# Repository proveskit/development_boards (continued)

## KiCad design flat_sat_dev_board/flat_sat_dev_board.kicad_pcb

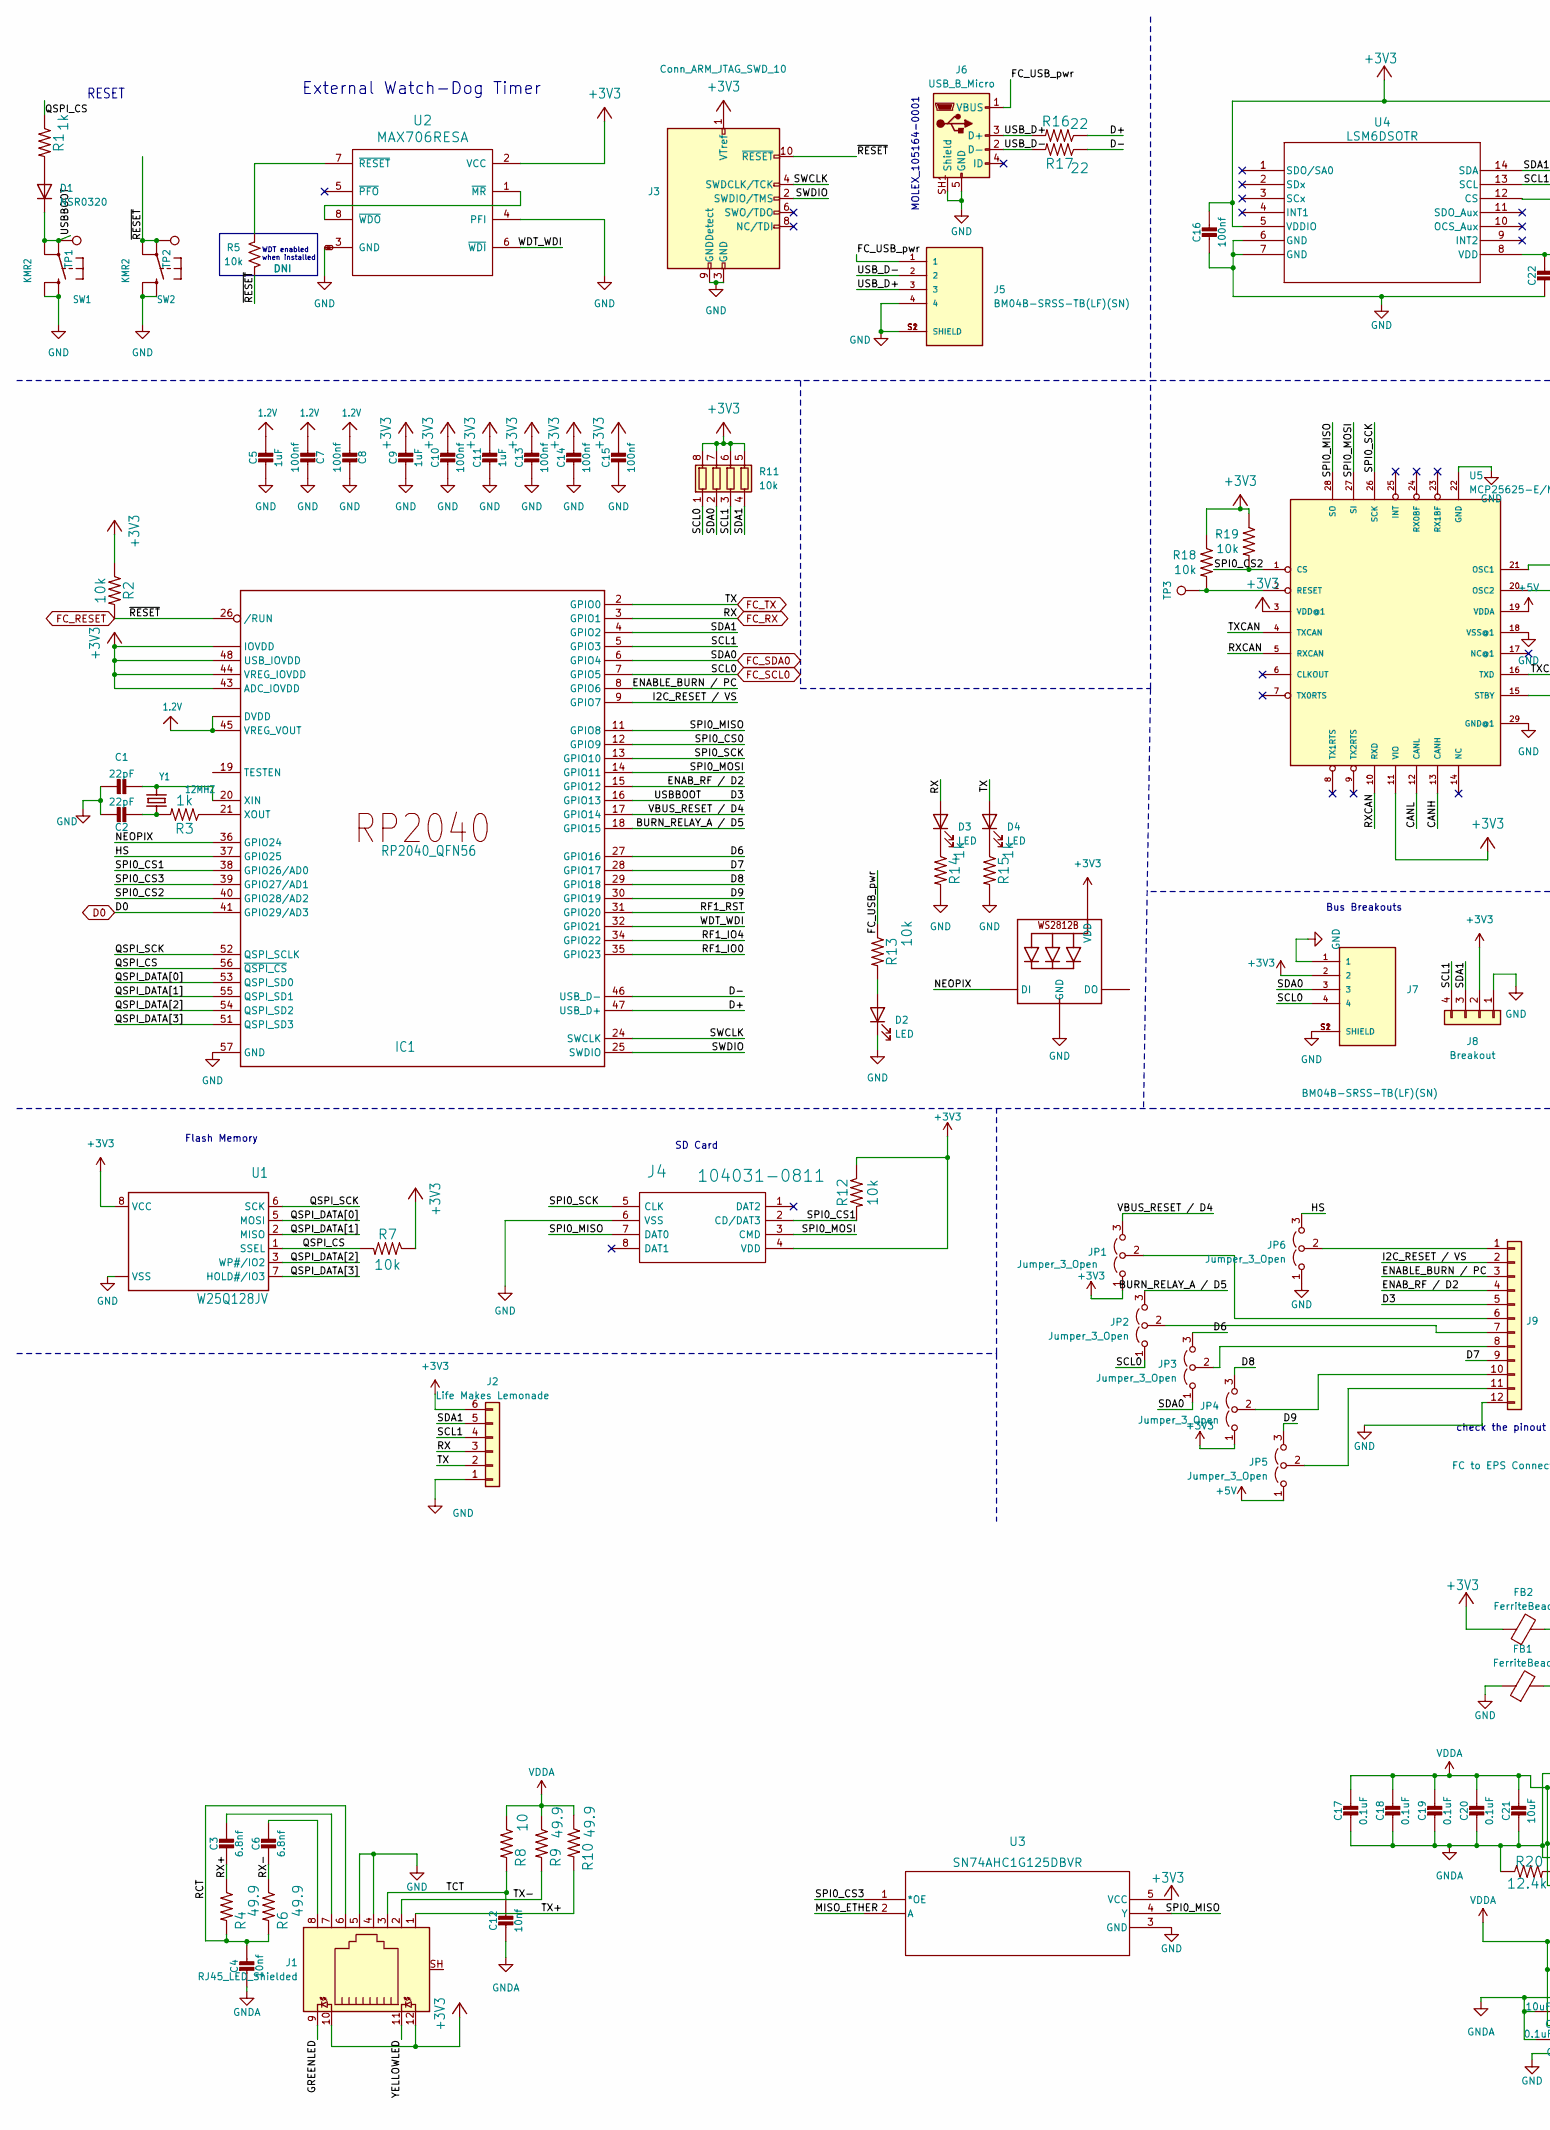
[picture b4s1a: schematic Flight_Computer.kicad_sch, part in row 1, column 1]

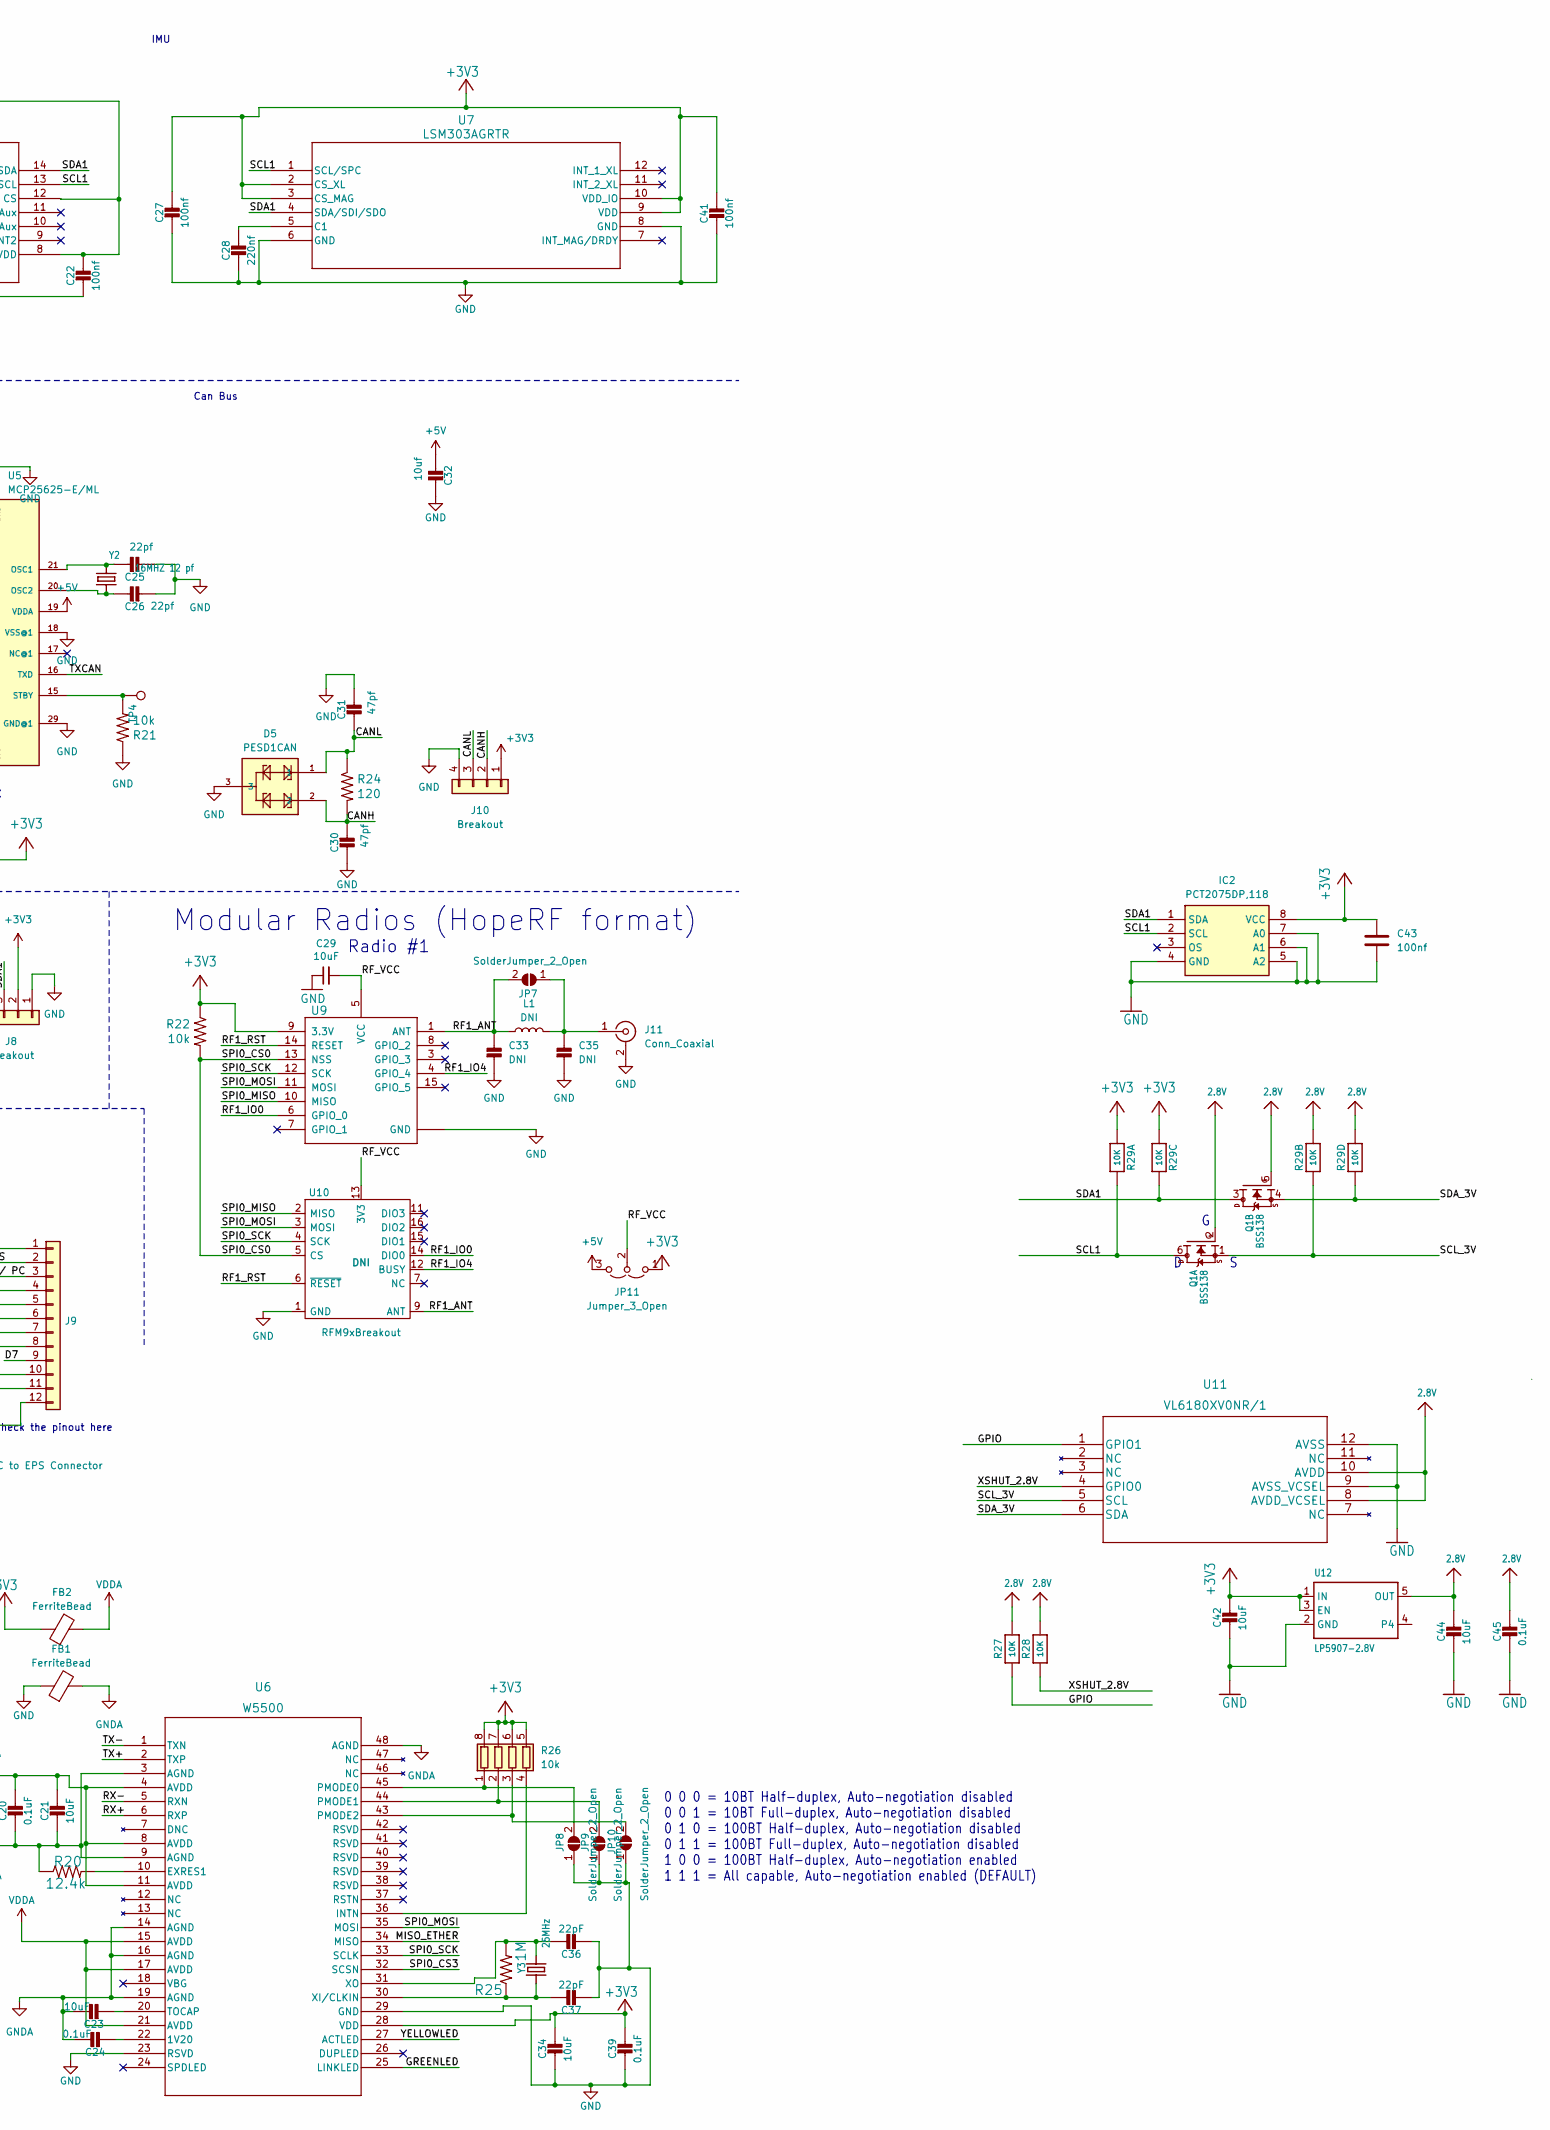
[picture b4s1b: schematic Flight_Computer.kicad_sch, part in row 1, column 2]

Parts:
C1, C2, C36, C37: 22pF; C_0402_1005Metric
C3, C6: 6.8nf; C_0402_1005Metric
C4, C12: 10nf; C_0402_1005Metric
C5, C9, C11: 1uF; C_0603_1608Metric
C7, C8, C10, C13, C14, C15, C16, C22, C27, C41: 100nf; C_0402_1005Metric
C17, C18, C19, C20, C24, C39, C45: 0.1uF; C_0603_1608Metric
C21, C23, C34, C42, C44: 10uF; C_0805_2012Metric
C25, C26: 22pf; C_0402_1005Metric
C28: 220nf; C_0402_1005Metric
C29: 10uF; C_0603_1608Metric
C30, C31: 47pf; C_0402_1005Metric
C32: 10uf; C_0603_1608Metric
C33, C35: DNI; C_0603_1608Metric
C43: 100nf; C_0603_1608Metric
D1: NSR0320; D_SOD-323F
D2, D3, D4: LED; LED_0603_1608Metric
D5: PESD1CAN; SOT-23-3
FB1, FB2: FerriteBead; R_0603_1608Metric
IC1: RP2040_QFN56; QFN-56-1EP_7x7mm_P0.4mm_EP3.2x3.2mm_ThermalVias
IC2: PCT2075DP,118; TSSOP-8_3x3mm_P0.65mm; Mouser Part Number 771-PCT2075DP118
J1: RJ45_LED_Shielded; RB1-125BAG1A_WIZ
J2: Life Makes Lemonade; PinHeader_1x06_P2.54mm_Vertical
J3: Conn_ARM_JTAG_SWD_10; JTAG_2X05_1.27MM_BOX_NOCREAM
J4: 104031-0811; microSD_HC_Molex_104031-0811; Manufacturer_Part_Number 104031-0811; Mouser Part Number 538-104031-0811
J5, J7: BM04B-SRSS-TB(LF)(SN); JST_BM04B-SRSS-TB(LF)(SN); PARTREV N/A
J6: USB_B_Micro; MOLEX_105164-0001
J8: Breakout; JST_SH_SM04B-SRSS-TB_1x04-1MP_P1.00mm_Horizontal
J9: FC to EPS Connector; Molex_Pico-Lock_504050-1291_1x12-1MP_P1.50mm_Horizontal
J10: Breakout; JST_SH_BM04B-SRSS-TB_1x04-1MP_P1.00mm_Vertical
J11: Conn_Coaxial; SMA_Amphenol_901-144_Vertical
JP1, JP2, JP3, JP4, JP5, JP6, JP11: Jumper_3_Open; SolderJumper-3_P1.3mm_Open_RoundedPad1.0x1.5mm_NumberLabels
JP7, JP8, JP9, JP10: SolderJumper_2_Open; SolderJumper-2_P1.3mm_Open_RoundedPad1.0x1.5mm
L1: DNI; R_0603_1608Metric
LED1: WS2812B_SK6812_1515; LED_WS2812B_PLCC4_5.0x5.0mm_P3.2mm
Q1: BSS138; SOT-363_SC-70-6
R1, R14, R15: 1k; R_0603_1608Metric
R2, R5, R7, R12, R13, R18, R19, R21, R22: 10k; R_0603_1608Metric
R3: 1k; R_0402_1005Metric
R4, R6, R9, R10: 49.9; R_0603_1608Metric
R8: 10; R_0603_1608Metric
R11, R26: 10k; R_Array_Convex_4x0603
R16, R17: 22; R_0603_1608Metric
R20: 12.4k; R_0603_1608Metric
R24: 120; R_0603_1608Metric
R25: 1M; R_0603_1608Metric
R27, R28: 10K; R_0603_1608Metric
R29: 10K; R_Array_Convex_4x0603
SW1, SW2: KMR2; BTN_KMR2_4.6X2.8
TP1: USBBOOT; TestPoint_Loop_D1.80mm_Drill1.0mm_Beaded
TP2, TP3: RESET; TestPoint_Loop_D1.80mm_Drill1.0mm_Beaded
TP4: Standby; TestPoint_Loop_D1.80mm_Drill1.0mm_Beaded
U1: W25Q128JV; SOIC-8_5.275x5.275mm_P1.27mm
U2: MAX706RESA; SO-8_3.9x4.9mm_P1.27mm; Manufacturer_Part_Number MAX706RESA
U3: SN74AHC1G125DBVR; SOT-23-5
U4: LSM6DSOTR; LGA-14_3x2.5mm_P0.5mm_LayoutBorder3x4y
U5: MCP25625-E/ML; QFN-28-1EP_6x6mm_P0.65mm_EP4.25x4.25mm
U6: W5500; LQFP-48_7x7mm_P0.5mm
U7: LSM303AGRTR; LGA-12_2x2mm_P0.5mm
U9: RFM98PW; Manufacturer_Part_Number RFM98PW
U10: RFM9xBreakout; HOPERF_RFM9XW_SMD
U11: VL6180XV0NR/1; VL6180
U12: LP5907-2.8V; SOT-23-5
Y1: 12MHZ; Crystal_SMD_2520-4Pin_2.5x2.0mm
Y2: 16MHZ 12 pf; Crystal_SMD_2520-4Pin_2.5x2.0mm
Y3: 25MHz; Crystal_SMD_3225-4Pin_3.2x2.5mm

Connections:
1.2V: C5.1, C7.2, C8.2, IC1.23 (DVDD), IC1.45 (VREG_VOUT), IC1.50 (DVDD); also elsewhere on the board
2.8V: C44.1, C45.1, Q1.2 (G), Q1.5 (G), R27.2, R28.2, R29.2 (1), R29.4 (1), U11.8 (AVDD_VCSEL), U11.10 (AVDD), U12.5 (OUT)
+3V3: C9.1, C10.1, C11.1, C13.1, C14.1, C15.1, C16.1, C22.1, C27.1, C34.1, C39.1, C41.1, C42.1, C43.1, FB2.1, IC1.1 (IOVDD), IC1.10 (IOVDD), IC1.22 (IOVDD), IC1.33 (IOVDD), IC1.42 (IOVDD), IC1.43 (ADC_IOVDD), IC1.44 (VREG_IOVDD), IC1.48 (USB_IOVDD), IC1.49 (IOVDD), IC2.8 (VCC), J1.10, J1.12, J2.6, J3.1 (VTref), J4.4 (VDD), J7.2, J8.2, J10.1, JP1.1 (A), JP4.1 (A), JP11.1 (A), LED1.1 (VDD), R2.1, R7.1, R11.5 (R4.2), R11.6 (R3.2), R11.7 (R2.2), R11.8 (R1.2), R12.1, R18.1, R19.1, R22.1, R26.5 (R4.2), R26.6 (R3.2), R26.7 (R2.2), R26.8 (R1.2), R29.1, R29.3 (1), U1.8 (VCC), U2.2 (VCC), U3.5 (VCC), U4.5 (VDDIO), U4.8 (VDD), U4.12 (CS), U5.3 (VDD@1), U5.11 (VIO), U6.28 (VDD), U7.2 (CS_XL), U7.3 (CS_MAG), U7.9 (VDD), U7.10 (VDD_IO), U9.9 (3.3V), U12.1 (IN), U12.3 (EN); also elsewhere on the board
+5V: C32.2, JP5.1 (A), JP11.3 (B), U5.19 (VDDA); also elsewhere on the board
/Flight Computer Stuff/BURN_RELAY_A / D5: IC1.18 (GPIO15), JP2.3 (B)
/Flight Computer Stuff/CANH: C30.2, D5.2, J10.2, R24.2, U5.13 (CANH)
/Flight Computer Stuff/CANL: C31.1, D5.1, J10.3, R24.1, U5.12 (CANL)
/Flight Computer Stuff/D3: D1.1 (K), IC1.16 (GPIO13), J9.5, SW1.A, SW1.A' (P1), TP1.1
/Flight Computer Stuff/D6: IC1.27 (GPIO16), JP3.3 (B)
/Flight Computer Stuff/D7: IC1.28 (GPIO17), J9.9
/Flight Computer Stuff/D8: IC1.29 (GPIO18), JP4.3 (B)
/Flight Computer Stuff/D9: IC1.30 (GPIO19), JP5.3 (B)
/Flight Computer Stuff/D+: IC1.47 (USB_D+), R16.1
/Flight Computer Stuff/D-: IC1.46 (USB_D-), R17.1
/Flight Computer Stuff/ENABLE_BURN / PC: IC1.8 (GPIO6), J9.3
/Flight Computer Stuff/ENAB_RF / D2: IC1.15 (GPIO12), J9.4
/Flight Computer Stuff/FC_USB_pwr: J5.1, J6.1 (VBUS), R13.1
/Flight Computer Stuff/GPIO: R27.1, U11.1 (GPIO1)
/Flight Computer Stuff/GREENLED: J1.9, U6.25 (LINKLED)
/Flight Computer Stuff/HS: IC1.37 (GPIO25), JP6.3 (B)
/Flight Computer Stuff/I2C_RESET / VS: IC1.9 (GPIO7), J9.2
/Flight Computer Stuff/MISO_ETHER: U3.2 (A), U6.34 (MISO)
/Flight Computer Stuff/NEOPIX: IC1.36 (GPIO24), LED1.4 (DI)
/Flight Computer Stuff/QSPI_CS: IC1.56 (~QSPI_CS), R1.1, R7.2, U1.1 (SSEL)
/Flight Computer Stuff/QSPI_DATA[0]: IC1.53 (QSPI_SD0), U1.5 (MOSI)
/Flight Computer Stuff/QSPI_DATA[1]: IC1.55 (QSPI_SD1), U1.2 (MISO)
/Flight Computer Stuff/QSPI_DATA[2]: IC1.54 (QSPI_SD2), U1.3 (WP#/IO2)
/Flight Computer Stuff/QSPI_DATA[3]: IC1.51 (QSPI_SD3), U1.7 (HOLD#/IO3)
/Flight Computer Stuff/QSPI_SCK: IC1.52 (QSPI_SCLK), U1.6 (SCK)
/Flight Computer Stuff/RCT: C4.1, J1.6, R4.2, R6.2
/Flight Computer Stuff/RF1_ANT: C33.1, JP7.2 (B), L1.1, U9.1 (ANT), U10.9 (ANT)
/Flight Computer Stuff/RF1_IO0: IC1.35 (GPIO23), U9.6 (GPIO_0), U10.14 (DIO0)
/Flight Computer Stuff/RF1_IO4: IC1.34 (GPIO22), U9.4 (GPIO_4), U10.12 (BUSY)
/Flight Computer Stuff/RF1_RST: IC1.31 (GPIO20), U9.14 (RESET), U10.6 (~RESET)
/Flight Computer Stuff/RF_VCC: C29.2, JP11.2 (C), U9.5 (VCC), U10.13 (3V3)
/Flight Computer Stuff/RX+: C3.2, R4.1, U6.6 (RXP)
/Flight Computer Stuff/RX-: C6.2, R6.1, U6.5 (RXN)
/Flight Computer Stuff/RXCAN: U5.5 (RXCAN), U5.10 (RXD)
/Flight Computer Stuff/SCL1: IC1.5 (GPIO3), IC2.2 (SCL), J2.4, J8.4, Q1.6 (D), R11.3 (R3.1), R29.8 (2), U4.13 (SCL), U7.1 (SCL/SPC)
/Flight Computer Stuff/SCL_3V: Q1.1 (S), R29.7 (2), U11.5 (SCL)
/Flight Computer Stuff/SDA1: IC1.4 (GPIO2), IC2.1 (SDA), J2.5, J8.3, Q1.3 (D), R11.4 (R4.1), R29.6 (2), U4.14 (SDA), U7.4 (SDA/SDI/SDO)
/Flight Computer Stuff/SDA_3V: Q1.4 (S), R29.5 (2), U11.6 (SDA)
/Flight Computer Stuff/SPI0_CS0: IC1.12 (GPIO9), R22.2, U9.13 (NSS), U10.5 (CS)
/Flight Computer Stuff/SPI0_CS1: IC1.38 (GPIO26/AD0), J4.2 (CD/DAT3), R12.2
/Flight Computer Stuff/SPI0_CS2: IC1.40 (GPIO28/AD2), R19.2, U5.1 (CS)
/Flight Computer Stuff/SPI0_CS3: IC1.39 (GPIO27/AD1), U3.1 (*OE), U6.32 (SCSN)
/Flight Computer Stuff/SPI0_MISO: IC1.11 (GPIO8), J4.7 (DAT0), U3.4 (Y), U5.28 (SO), U9.10 (MISO), U10.2 (MISO)
/Flight Computer Stuff/SPI0_MOSI: IC1.14 (GPIO11), J4.3 (CMD), U5.27 (SI), U6.35 (MOSI), U9.11 (MOSI), U10.3 (MOSI)
/Flight Computer Stuff/SPI0_SCK: IC1.13 (GPIO10), J4.5 (CLK), U5.26 (SCK), U6.33 (SCLK), U9.12 (SCK), U10.4 (SCK)
/Flight Computer Stuff/SWCLK: IC1.24 (SWCLK), J3.4 (SWDCLK/TCK)
/Flight Computer Stuff/SWDIO: IC1.25 (SWDIO), J3.2 (SWDIO/TMS)
/Flight Computer Stuff/TCT: C12.1, J1.3, R8.2
/Flight Computer Stuff/TX+: J1.1, R10.2, U6.2 (TXP)
/Flight Computer Stuff/TX-: J1.2, R9.2, U6.1 (TXN)
/Flight Computer Stuff/TXCAN: U5.4 (TXCAN), U5.16 (TXD)
/Flight Computer Stuff/USB_D+: J5.3, J6.3 (D+), R16.2
/Flight Computer Stuff/USB_D-: J5.2, J6.2 (D-), R17.2
/Flight Computer Stuff/VBUS_RESET / D4: IC1.17 (GPIO14), JP1.3 (B)
/Flight Computer Stuff/WDT_WDI: IC1.32 (GPIO21), U2.6 (~WDI)
/Flight Computer Stuff/XSHUT_2.8V: R28.1, U11.4 (GPIO0)
/Flight Computer Stuff/YELLOWLED: J1.11, U6.27 (ACTLED)
D0: IC1.41 (GPIO29/AD3); also elsewhere on the board
FC_RESET: IC1.26 (/RUN), J3.10 (~RESET), R2.2, R5.1, SW2.A, SW2.A' (P1), TP2.1
FC_RX: D3.2 (A), IC1.3 (GPIO1), J2.3; also elsewhere on the board
FC_SCL0: IC1.7 (GPIO5), J7.4, JP2.1 (A), R11.1 (R1.1); also elsewhere on the board
FC_SDA0: IC1.6 (GPIO4), J7.3, JP3.1 (A), R11.2 (R2.1); also elsewhere on the board
FC_TX: D4.2 (A), IC1.2 (GPIO0), J2.2; also elsewhere on the board
GND: C1.1, C2.1, C5.2, C7.1, C8.1, C9.2, C10.2, C11.2, C13.2, C14.2, C15.2, C16.2, C22.2, C25.2, C26.2, C27.2, C28.2, C29.1, C30.1, C31.2, C32.1, C33.2, C34.2, C35.2, C36.2, C37.2, C39.2, C41.2, C42.2, C43.2, C44.2, C45.2, D2.1 (K), D5.3, FB1.1, IC1.57 (GND), IC2.4 (GND), IC2.5 (A2), IC2.6 (A1), IC2.7 (A0), J1.4, J1.5, J2.1, J3.3 (GND), J3.5 (GND), J3.9 (GNDDetect), J4.6 (VSS), J5.4, J5.S1 (SHIELD), J5.S2 (SHIELD), J6.5 (GND), J6.SH1 (Shield), J7.1, J7.S1 (SHIELD), J7.S2 (SHIELD), J8.1, J9.12, J10.4, J11.2 (Ext), JP6.1 (A), JP8.1 (A), JP9.1 (A), JP10.1 (A), LED1.3 (GND), R14.2, R15.2, R21.1, SW1.B (S), SW1.B' (S1), SW2.B (S), SW2.B' (S1), U1.4 (VSS), U1.PAD (VSS), U2.3 (GND), U2.4 (PFI), U3.3 (GND), U4.6 (GND), U4.7 (GND), U5.18 (VSS@1), U5.22 (GND), U5.29 (GND@1), U6.23 (RSVD), U6.29 (GND), U7.6 (GND), U7.8 (GND), U9.2 (GND), U9.16 (GND), U9.17 (GND), U10.1 (GND), U10.8 (GND), U10.10 (GND), U11.9 (AVSS_VCSEL), U11.12 (AVSS), U12.2 (GND); also elsewhere on the board
GNDA: C4.2, C12.2, C17.2, C18.2, C19.2, C20.2, C21.2, C23.1, C24.1, FB1.2, R20.1, U6.3 (AGND), U6.9 (AGND), U6.14 (AGND), U6.16 (AGND), U6.19 (AGND), U6.48 (AGND)
unnamed: C2.2, R3.2, Y1.1
unnamed: C3.1, J1.7
unnamed: C6.1, J1.8
unnamed: D1.2 (A), R1.2
unnamed: D2.2 (A), R13.2
unnamed: D3.1 (K), R14.1
unnamed: D4.1 (K), R15.1
unnamed: C1.2, IC1.20 (XIN), Y1.3 (2)
unnamed: IC1.21 (XOUT), R3.1
unnamed: J9.1, JP6.2 (C)
unnamed: J9.6, JP1.2 (C)
unnamed: J9.7, JP2.2 (C)
unnamed: J9.8, JP3.2 (C)
unnamed: J9.10, JP4.2 (C)
unnamed: J9.11, JP5.2 (C)
unnamed: C35.1, J11.1 (In), JP7.1 (A), L1.2
unnamed: JP8.2 (B), R26.1 (R1.1), U6.45 (PMODE0)
unnamed: JP9.2 (B), R26.2 (R2.1), U6.44 (PMODE1)
unnamed: JP10.2 (B), R26.3 (R3.1), U6.43 (PMODE2)
unnamed: R26.4 (R4.1), U6.36 (INTN)
unnamed: U2.1 (~MR), U2.8 (~WDO)
unnamed: R5.2, U2.7 (~RESET)
unnamed: C25.1, U5.21 (OSC1), Y2.3 (2)
unnamed: C26.1, U5.20 (OSC2), Y2.1
unnamed: R18.2, TP3.1, U5.2 (RESET)
unnamed: R21.2, TP4.1, U5.15 (STBY)
unnamed: C24.2, U6.22 (1V20)
unnamed: R20.2, U6.10 (EXRES1)
unnamed: C23.2, U6.20 (TOCAP)
unnamed: C37.1, R25.1, U6.30 (XI/CLKIN), Y3.1
unnamed: C36.1, R25.2, U6.31 (XO), Y3.3 (2)
unnamed: C28.1, U7.5 (C1)
VDDA: C17.1, C18.1, C19.1, C20.1, C21.1, FB2.2, R8.1, R9.1, R10.1, U6.4 (AVDD), U6.8 (AVDD), U6.11 (AVDD), U6.15 (AVDD), U6.17 (AVDD), U6.21 (AVDD)

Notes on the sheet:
Bus Breakouts
Can Bus
Radio #1
Modular Radios (HopeRF format)
0 0 0 = 10BT Half-duplex, Auto-negotiation disabled 0 0 1 = 10BT Full-duplex, Auto-negotiation disabled 0 1 0 = 100BT Half-duplex, Auto-negotiation disabled 0 1 1 = 100BT Full-duplex, Auto-negotiation disabled 1 0 0 = 100BT Half-duplex, Auto-negotiation enabled 1 1 1 = All capable, Auto-negotiation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
MOLEX_105164-0001
check the pinout here
RESET
IMU
Flash Memory
WDT enabled when installed
External Watch-Dog Timer
SD Card

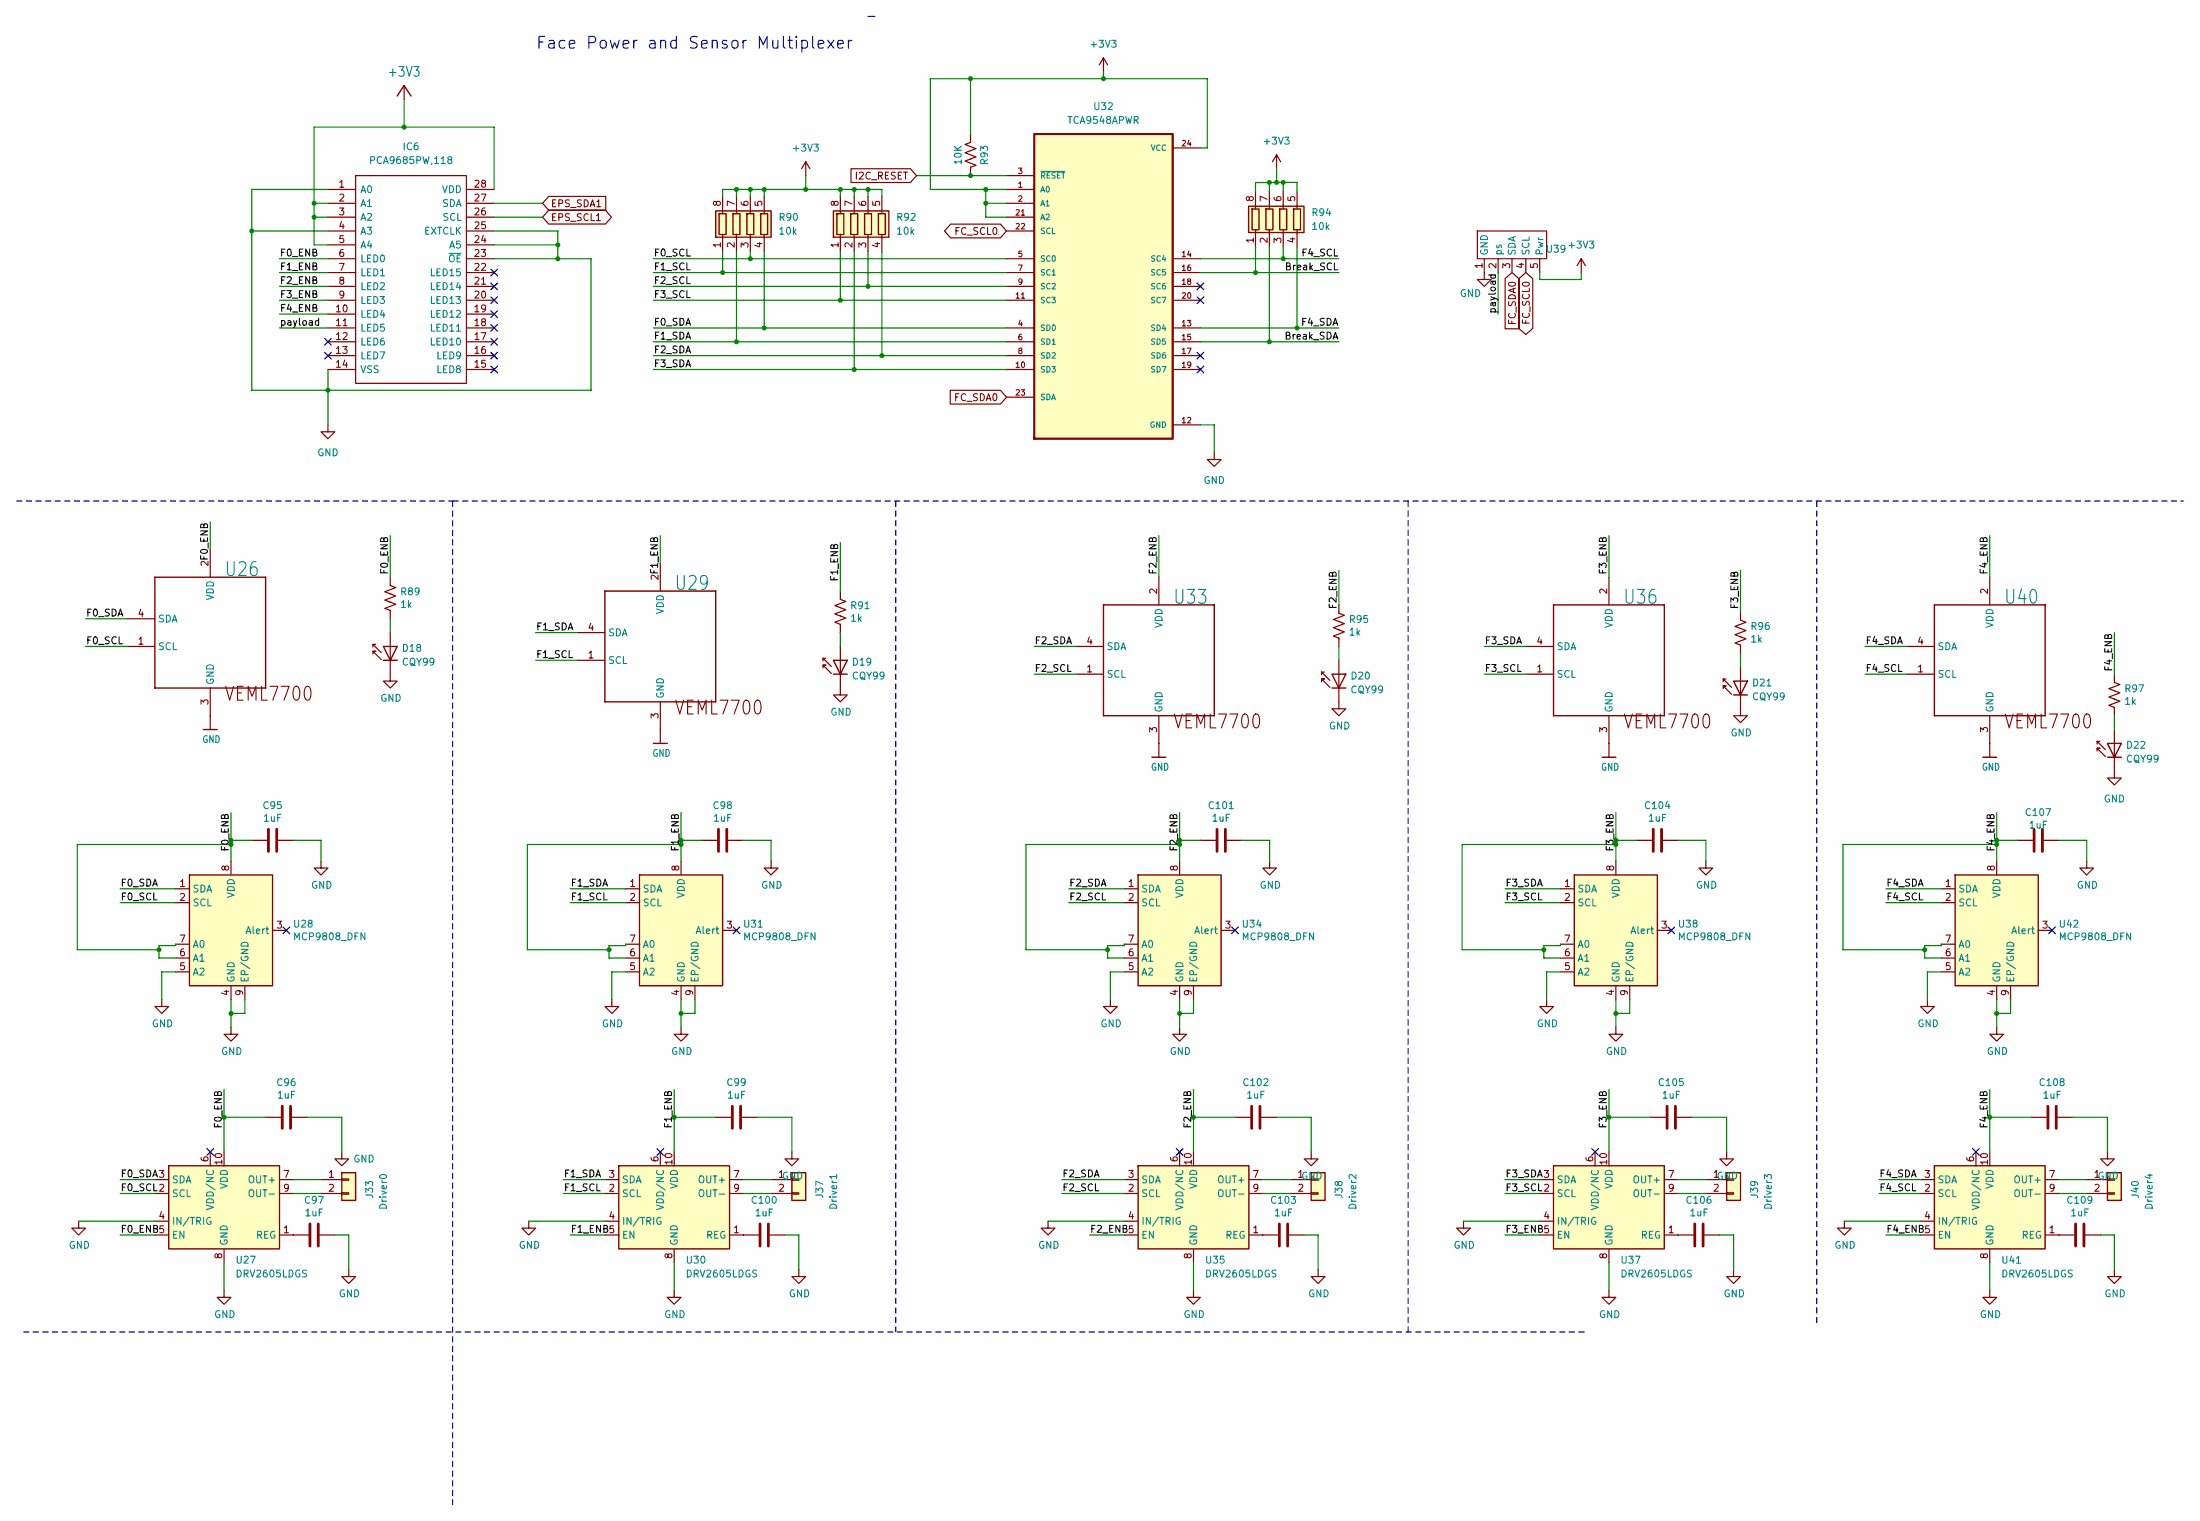
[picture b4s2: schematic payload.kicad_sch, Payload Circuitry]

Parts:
C95, C96, C97, C98, C99, C100, C101, C102, C103, C104, C105, C106, C107, C108, C109: 1uF; C_0805_2012Metric
D18, D19, D20, D21, D22: CQY99; LED_0603_1608Metric
IC6: PCA9685PW,118; TSSOP-28_8x9.7mm_P0.65mm; Mouser Part Number 771-PCA9685PW,118
J33: Driver0; MOLEX_504050-0291
J37: Driver1; MOLEX_504050-0291
J38: Driver2; MOLEX_504050-0291
J39: Driver3; MOLEX_504050-0291
J40: Driver4; MOLEX_504050-0291
R89, R91, R95, R96, R97: 1k; R_0603_1608Metric
R90, R92, R94: 10k; R_Array_Convex_4x0603
R93: 10K; R_0603_1608Metric
U26, U29, U33, U36, U40: VEML7700; XDCR_VEML7700-TT
U27, U30, U35, U37, U41: DRV2605LDGS; VSSOP-10_3x3mm_P0.5mm
U28, U31, U34, U38, U42: MCP9808_DFN; MSOP-8-1EP_3x3mm_P0.65mm_EP2.5x3mm_Mask1.73x2.36mm
U32: TCA9548APWR; TSSOP-24_6.1x7.8mm_P0.65mm
U39: camera_daughter

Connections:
+3V3: IC6.2 (A1), IC6.3 (A2), IC6.5 (A4), IC6.28 (VDD), R90.5 (R4.2), R90.6 (R3.2), R90.7 (R2.2), R90.8 (R1.2), R92.5 (R4.2), R92.6 (R3.2), R92.7 (R2.2), R92.8 (R1.2), R93.1, R94.5 (R4.2), R94.6 (R3.2), R94.7 (R2.2), R94.8 (R1.2), U32.1 (A0), U32.2 (A1), U32.21 (A2), U32.24 (VCC), U39.5 (Pwr); also elsewhere on the board
/Payload Stuff/Break_SCL: R94.1 (R1.1), U32.16 (SC5)
/Payload Stuff/Break_SDA: R94.2 (R2.1), U32.15 (SD5)
/Payload Stuff/F0_ENB: C95.1, C96.1, IC6.6 (LED0), R89.1, U26.2 (VDD), U27.5 (EN), U27.10 (VDD), U28.6 (A1), U28.7 (A0), U28.8 (VDD)
/Payload Stuff/F0_SCL: R90.3 (R3.1), U26.1 (SCL), U27.2 (SCL), U28.2 (SCL), U32.5 (SC0)
/Payload Stuff/F0_SDA: R90.4 (R4.1), U26.4 (SDA), U27.3 (SDA), U28.1 (SDA), U32.4 (SD0)
/Payload Stuff/F1_ENB: C98.1, C99.1, IC6.7 (LED1), R91.1, U29.2 (VDD), U30.5 (EN), U30.10 (VDD), U31.6 (A1), U31.7 (A0), U31.8 (VDD)
/Payload Stuff/F1_SCL: R90.1 (R1.1), U29.1 (SCL), U30.2 (SCL), U31.2 (SCL), U32.7 (SC1)
/Payload Stuff/F1_SDA: R90.2 (R2.1), U29.4 (SDA), U30.3 (SDA), U31.1 (SDA), U32.6 (SD1)
/Payload Stuff/F2_ENB: C101.1, C102.1, IC6.8 (LED2), R95.1, U33.2 (VDD), U34.6 (A1), U34.7 (A0), U34.8 (VDD), U35.5 (EN), U35.10 (VDD)
/Payload Stuff/F2_SCL: R92.3 (R3.1), U32.9 (SC2), U33.1 (SCL), U34.2 (SCL), U35.2 (SCL)
/Payload Stuff/F2_SDA: R92.4 (R4.1), U32.8 (SD2), U33.4 (SDA), U34.1 (SDA), U35.3 (SDA)
/Payload Stuff/F3_ENB: C104.1, C105.1, IC6.9 (LED3), R96.1, U36.2 (VDD), U37.5 (EN), U37.10 (VDD), U38.6 (A1), U38.7 (A0), U38.8 (VDD)
/Payload Stuff/F3_SCL: R92.1 (R1.1), U32.11 (SC3), U36.1 (SCL), U37.2 (SCL), U38.2 (SCL)
/Payload Stuff/F3_SDA: R92.2 (R2.1), U32.10 (SD3), U36.4 (SDA), U37.3 (SDA), U38.1 (SDA)
/Payload Stuff/F4_ENB: C107.1, C108.1, IC6.10 (LED4), R97.1, U40.2 (VDD), U41.5 (EN), U41.10 (VDD), U42.6 (A1), U42.7 (A0), U42.8 (VDD)
/Payload Stuff/F4_SCL: R94.3 (R3.1), U32.14 (SC4), U40.1 (SCL), U41.2 (SCL), U42.2 (SCL)
/Payload Stuff/F4_SDA: R94.4 (R4.1), U32.13 (SD4), U40.4 (SDA), U41.3 (SDA), U42.1 (SDA)
/Payload Stuff/payload: IC6.11 (LED5), U39.2 (ps)
EPS_SCL1: IC6.26 (SCL); also elsewhere on the board
EPS_SDA1: IC6.27 (SDA); also elsewhere on the board
FC_SCL0: U32.22 (SCL), U39.4 (SCL); also elsewhere on the board
FC_SDA0: U32.23 (SDA), U39.3 (SDA); also elsewhere on the board
GND: C95.2, C96.2, C97.2, C98.2, C99.2, C100.2, C101.2, C102.2, C103.2, C104.2, C105.2, C106.2, C107.2, C108.2, C109.2, D18.1 (K), D19.1 (K), D20.1 (K), D21.1 (K), D22.1 (K), IC6.1 (A0), IC6.4 (A3), IC6.14 (VSS), IC6.23 (~OE), IC6.24 (A5), IC6.25 (EXTCLK), U26.3 (GND), U27.4 (IN/TRIG), U27.8 (GND), U28.4 (GND), U28.5 (A2), U28.9 (EP/GND), U29.3 (GND), U30.4 (IN/TRIG), U30.8 (GND), U31.4 (GND), U31.5 (A2), U31.9 (EP/GND), U32.12 (GND), U33.3 (GND), U34.4 (GND), U34.5 (A2), U34.9 (EP/GND), U35.4 (IN/TRIG), U35.8 (GND), U36.3 (GND), U37.4 (IN/TRIG), U37.8 (GND), U38.4 (GND), U38.5 (A2), U38.9 (EP/GND), U39.1 (GND), U40.3 (GND), U41.4 (IN/TRIG), U41.8 (GND), U42.4 (GND), U42.5 (A2), U42.9 (EP/GND); also elsewhere on the board
I2C_RESET: R93.2, U32.3 (~RESET)
unnamed: D18.2 (A), R89.2
unnamed: D19.2 (A), R91.2
unnamed: D20.2 (A), R95.2
unnamed: D21.2 (A), R96.2
unnamed: D22.2 (A), R97.2
unnamed: J33.1, U27.7 (OUT+)
unnamed: J33.2, U27.9 (OUT-)
unnamed: J37.1, U30.7 (OUT+)
unnamed: J37.2, U30.9 (OUT-)
unnamed: J38.1, U35.7 (OUT+)
unnamed: J38.2, U35.9 (OUT-)
unnamed: J39.1, U37.7 (OUT+)
unnamed: J39.2, U37.9 (OUT-)
unnamed: J40.1, U41.7 (OUT+)
unnamed: J40.2, U41.9 (OUT-)
unnamed: C97.1, U27.1 (REG)
unnamed: C100.1, U30.1 (REG)
unnamed: C103.1, U35.1 (REG)
unnamed: C106.1, U37.1 (REG)
unnamed: C109.1, U41.1 (REG)

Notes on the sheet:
Face Power and Sensor Multiplexer
